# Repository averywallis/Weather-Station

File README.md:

# Weather-Station
 KiCad files for a homemade Weather Station

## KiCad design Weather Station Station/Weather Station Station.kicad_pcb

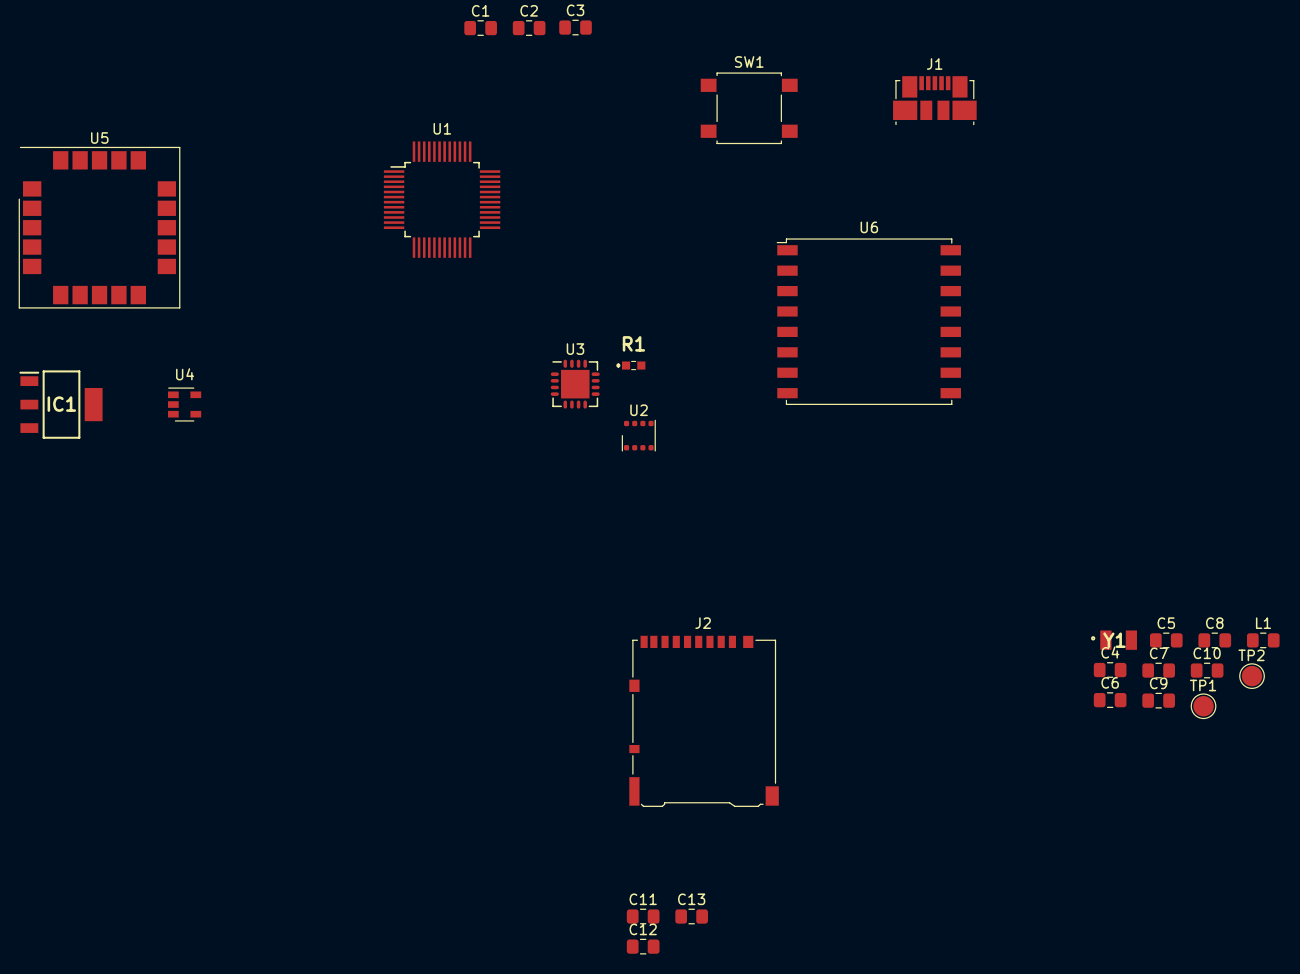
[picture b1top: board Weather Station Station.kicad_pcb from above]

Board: 2 copper layers, 28 parts (0 on the bottom side), 13 nets, no tracks yet.

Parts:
C1, C5, C8, C13: 0.1uF; C_0805_2012Metric_Pad1.15x1.40mm_HandSolder
C2, C4, C7: 10uF; C_0805_2012Metric_Pad1.15x1.40mm_HandSolder
C3, C6, C11, C12: 1uF; C_0805_2012Metric_Pad1.15x1.40mm_HandSolder
C9, C10: 10pF; C_0805_2012Metric_Pad1.15x1.40mm_HandSolder
IC1: MIC39100-3.3WS; SOT230P700X180-4N
J1: USB_B_Micro; USB_Micro-B_Molex_47346-0001
J2: Micro_SD_Card_Det; microSD_HC_Hirose_DM3AT-SF-PEJM5
L1: 10uH; L_0805_2012Metric_Pad1.15x1.40mm_HandSolder
R1: ALS-PT19-315C_L177_TR8; ALSPT19315CL177TR8
SW1: SW_SPST; SW_SPST_B3S-1000
TP1, TP2: TestPoint; TestPoint_Pad_D2.0mm
U1: ATSAMD21G18A-AUT-MCU_Microchip_SAMD_Redone; TQFP-48_7x7mm_P0.5mm_hand_solder
U2: BME680; Bosch_LGA-8_3x3mm_P0.8mm_ClockwisePinNumbering
U3: AS3935; MLPQ-16-1EP_4x4mm_P0.65mm_EP2.8x2.8mm
U4: MCP73831-2-OT; SOT-23-5
U5: ublox_SAM-M8Q
U6: RFM95W-915S2; HOPERF_RFM9XW_SMD
Y1: 32768Hz; ABS-07

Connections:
+3V3: C1.1, C2.1, C4.1, C5.1, C12.1, C13.1, IC1.3, L1.1, U1.17, U1.36
/Power/VBUS: C11.1, IC1.1, J1.1
/SAMD21/AREF: C3.1, U1.4
/SAMD21/SWCLK: TP1.1, U1.45
/SAMD21/SWDIO: TP2.1, U1.46
/SAMD21/~RESET_SAMD: SW1.1, U1.40
GND: C1.2, C2.2, C3.2, C4.2, C5.2, C6.2, C7.2, C8.2, C9.2, C10.2, C11.2, C12.2, C13.2, IC1.2, IC1.4, J1.5, SW1.2
unnamed: C6.1, U1.43
unnamed: C7.1, C8.1, L1.2, U1.6
unnamed: C9.1, U1.1, Y1.1
unnamed: C10.1, U1.2, Y1.2
unnamed: U1.18, U1.35, U1.42
unnamed: U5.1, U5.4, U5.5, U5.6, U5.10, U5.11, U5.15, U5.16, U5.20

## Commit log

2022-01-29 Create LICENSE
